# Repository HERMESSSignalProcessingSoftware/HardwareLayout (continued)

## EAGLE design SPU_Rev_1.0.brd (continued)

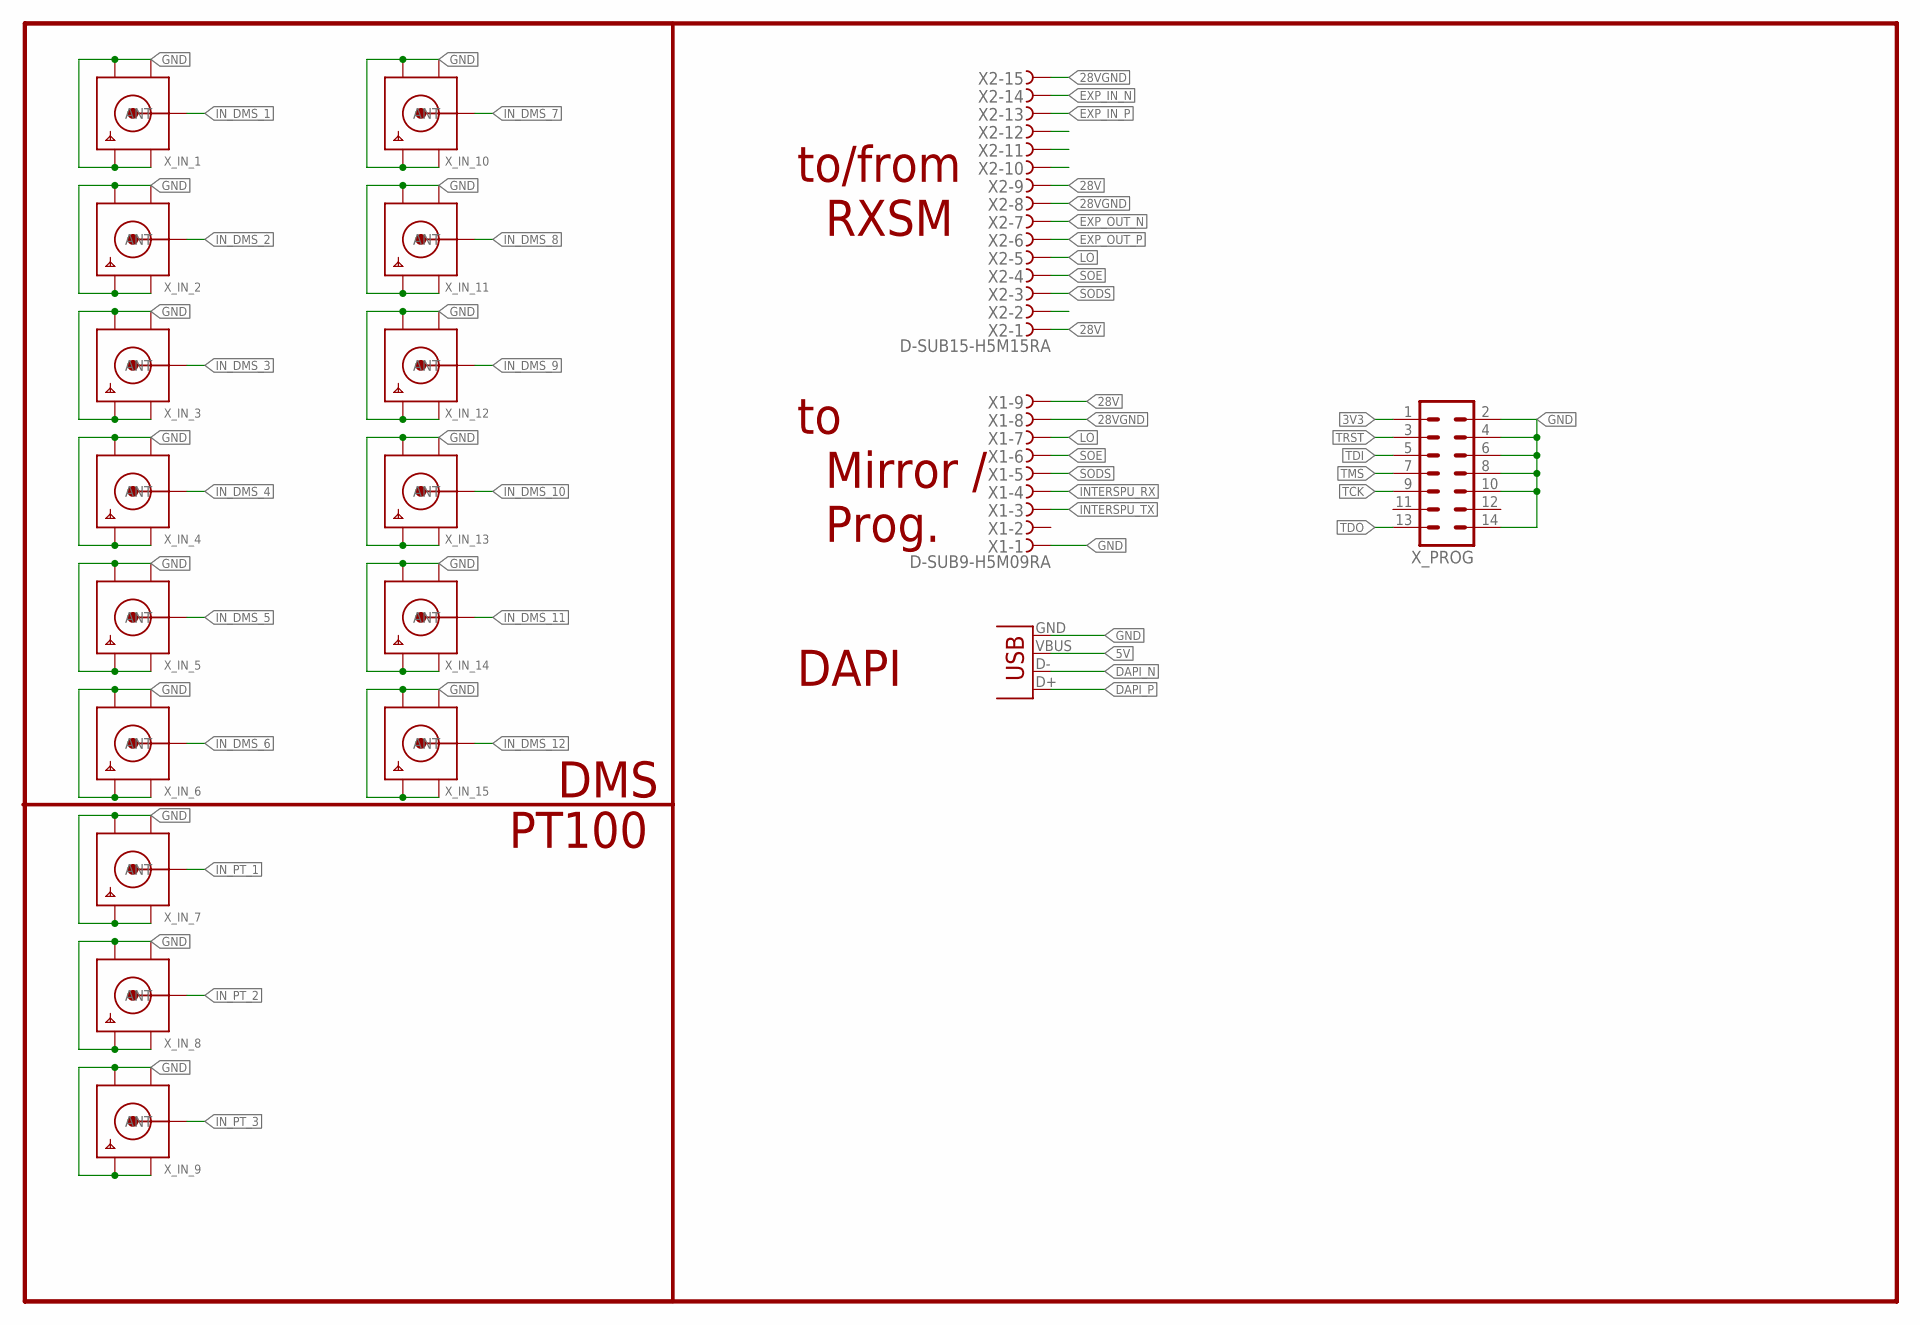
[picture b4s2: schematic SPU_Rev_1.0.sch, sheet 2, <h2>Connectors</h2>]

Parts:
X1: D-SUB9-H5M09RA; H5M09RA
X2: D-SUB15-H5M15RA; H5M15RA
X3: USBPTH; USB-B-PTH
X_IN_1, X_IN_2, X_IN_3, X_IN_4, X_IN_5, X_IN_6, X_IN_7, X_IN_8, X_IN_9, X_IN_10, X_IN_11, X_IN_12, X_IN_13, X_IN_14, X_IN_15: SMACONNECTOR_EDGE; SMA_EDGELAUNCH
X_PROG: MA07-2

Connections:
3V3: X_PROG.1; also elsewhere on the board
5V: X3.VBUS; also elsewhere on the board
28V: X1.9, X2.1, X2.9; also elsewhere on the board
28VGND: X1.8, X2.8, X2.15; also elsewhere on the board
DAPI_N: X3.D-; also elsewhere on the board
DAPI_P: X3.D+; also elsewhere on the board
EXP_IN_N: X2.14; also elsewhere on the board
EXP_IN_P: X2.13; also elsewhere on the board
EXP_OUT_N: X2.7; also elsewhere on the board
EXP_OUT_P: X2.6; also elsewhere on the board
GND: X1.1, X3.GND, X_IN_1.GND@1 (GND4), X_IN_1.GND@2 (GND3), X_IN_1.GND@3 (GND2), X_IN_1.GND@4 (GND1), X_IN_2.GND@1 (GND4), X_IN_2.GND@2 (GND3), X_IN_2.GND@3 (GND2), X_IN_2.GND@4 (GND1), X_IN_3.GND@1 (GND4), X_IN_3.GND@2 (GND3), X_IN_3.GND@3 (GND2), X_IN_3.GND@4 (GND1), X_IN_4.GND@1 (GND4), X_IN_4.GND@2 (GND3), X_IN_4.GND@3 (GND2), X_IN_4.GND@4 (GND1), X_IN_5.GND@1 (GND4), X_IN_5.GND@2 (GND3), X_IN_5.GND@3 (GND2), X_IN_5.GND@4 (GND1), X_IN_6.GND@1 (GND4), X_IN_6.GND@2 (GND3), X_IN_6.GND@3 (GND2), X_IN_6.GND@4 (GND1), X_IN_7.GND@1 (GND4), X_IN_7.GND@2 (GND3), X_IN_7.GND@3 (GND2), X_IN_7.GND@4 (GND1), X_IN_8.GND@1 (GND4), X_IN_8.GND@2 (GND3), X_IN_8.GND@3 (GND2), X_IN_8.GND@4 (GND1), X_IN_9.GND@1 (GND4), X_IN_9.GND@2 (GND3), X_IN_9.GND@3 (GND2), X_IN_9.GND@4 (GND1), X_IN_10.GND@1 (GND4), X_IN_10.GND@2 (GND3), X_IN_10.GND@3 (GND2), X_IN_10.GND@4 (GND1), X_IN_11.GND@1 (GND4), X_IN_11.GND@2 (GND3), X_IN_11.GND@3 (GND2), X_IN_11.GND@4 (GND1), X_IN_12.GND@1 (GND4), X_IN_12.GND@2 (GND3), X_IN_12.GND@3 (GND2), X_IN_12.GND@4 (GND1), X_IN_13.GND@1 (GND4), X_IN_13.GND@2 (GND3), X_IN_13.GND@3 (GND2), X_IN_13.GND@4 (GND1), X_IN_14.GND@1 (GND4), X_IN_14.GND@2 (GND3), X_IN_14.GND@3 (GND2), X_IN_14.GND@4 (GND1), X_IN_15.GND@1 (GND4), X_IN_15.GND@2 (GND3), X_IN_15.GND@3 (GND2), X_IN_15.GND@4 (GND1), X_PROG.2, X_PROG.4, X_PROG.6, X_PROG.8, X_PROG.10, X_PROG.14; also elsewhere on the board
INTERSPU_RX: X1.4; also elsewhere on the board
INTERSPU_TX: X1.3; also elsewhere on the board
IN_DMS_1: X_IN_1.P (ANT); also elsewhere on the board
IN_DMS_2: X_IN_2.P (ANT); also elsewhere on the board
IN_DMS_3: X_IN_3.P (ANT); also elsewhere on the board
IN_DMS_4: X_IN_4.P (ANT); also elsewhere on the board
IN_DMS_5: X_IN_5.P (ANT); also elsewhere on the board
IN_DMS_6: X_IN_6.P (ANT); also elsewhere on the board
IN_DMS_7: X_IN_10.P (ANT); also elsewhere on the board
IN_DMS_8: X_IN_11.P (ANT); also elsewhere on the board
IN_DMS_9: X_IN_12.P (ANT); also elsewhere on the board
IN_DMS_10: X_IN_13.P (ANT); also elsewhere on the board
IN_DMS_11: X_IN_14.P (ANT); also elsewhere on the board
IN_DMS_12: X_IN_15.P (ANT); also elsewhere on the board
IN_PT_1: X_IN_7.P (ANT); also elsewhere on the board
IN_PT_2: X_IN_8.P (ANT); also elsewhere on the board
IN_PT_3: X_IN_9.P (ANT); also elsewhere on the board
LO: X1.7, X2.5; also elsewhere on the board
SODS: X1.5, X2.3; also elsewhere on the board
SOE: X1.6, X2.4; also elsewhere on the board
TCK: X_PROG.9; also elsewhere on the board
TDI: X_PROG.5; also elsewhere on the board
TDO: X_PROG.13; also elsewhere on the board
TMS: X_PROG.7; also elsewhere on the board
TRST: X_PROG.3; also elsewhere on the board

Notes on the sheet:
DMS
PT100
DAPI
to/from RXSM
to Mirror / Prog.

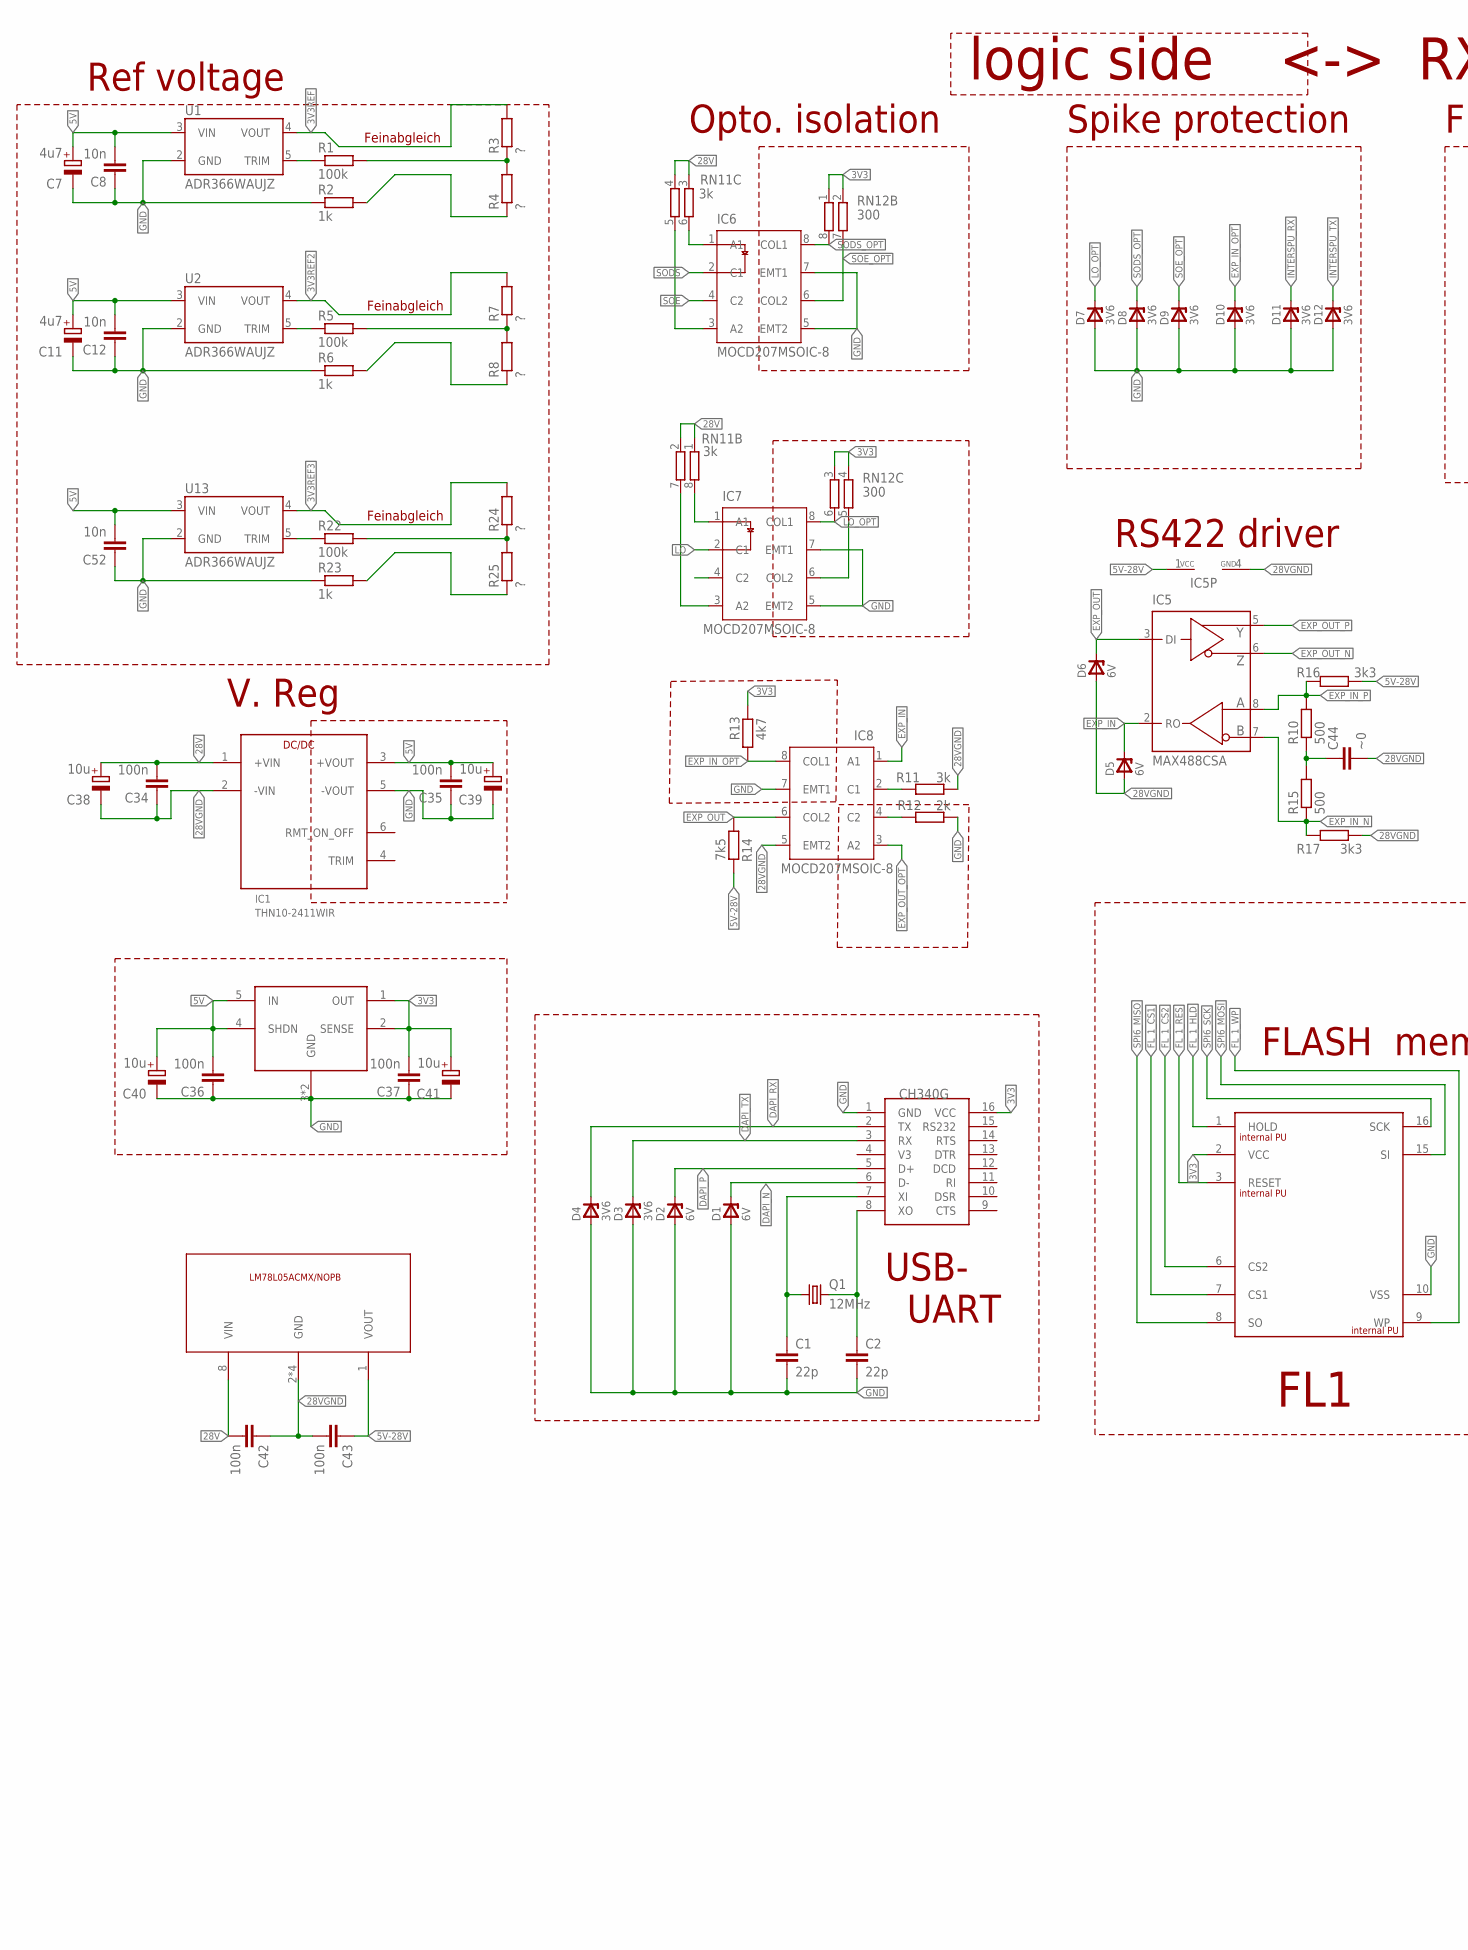
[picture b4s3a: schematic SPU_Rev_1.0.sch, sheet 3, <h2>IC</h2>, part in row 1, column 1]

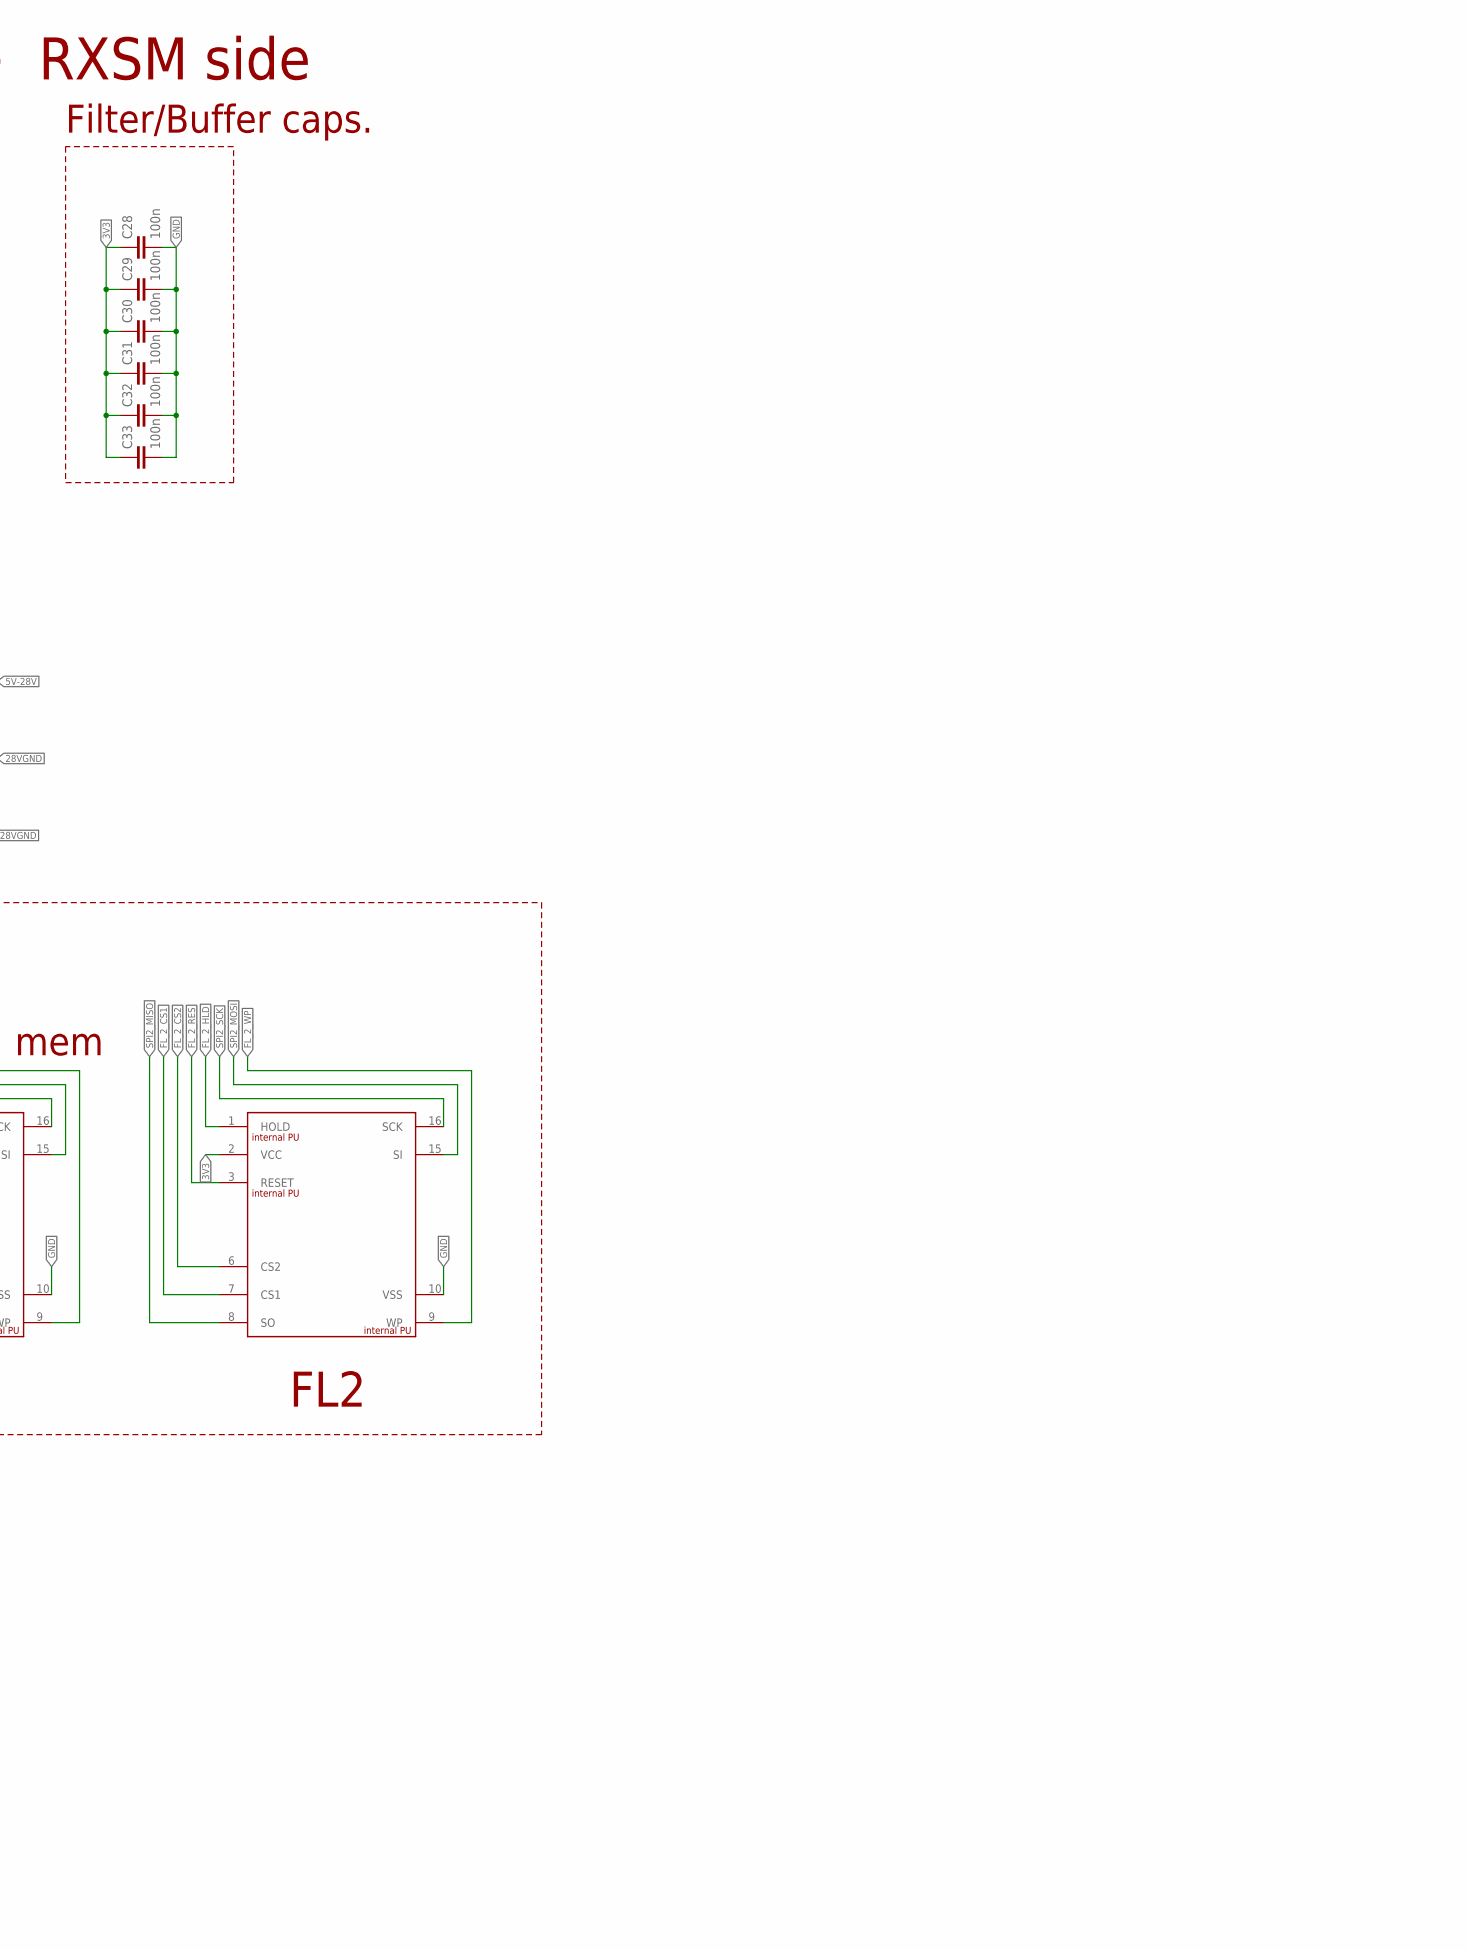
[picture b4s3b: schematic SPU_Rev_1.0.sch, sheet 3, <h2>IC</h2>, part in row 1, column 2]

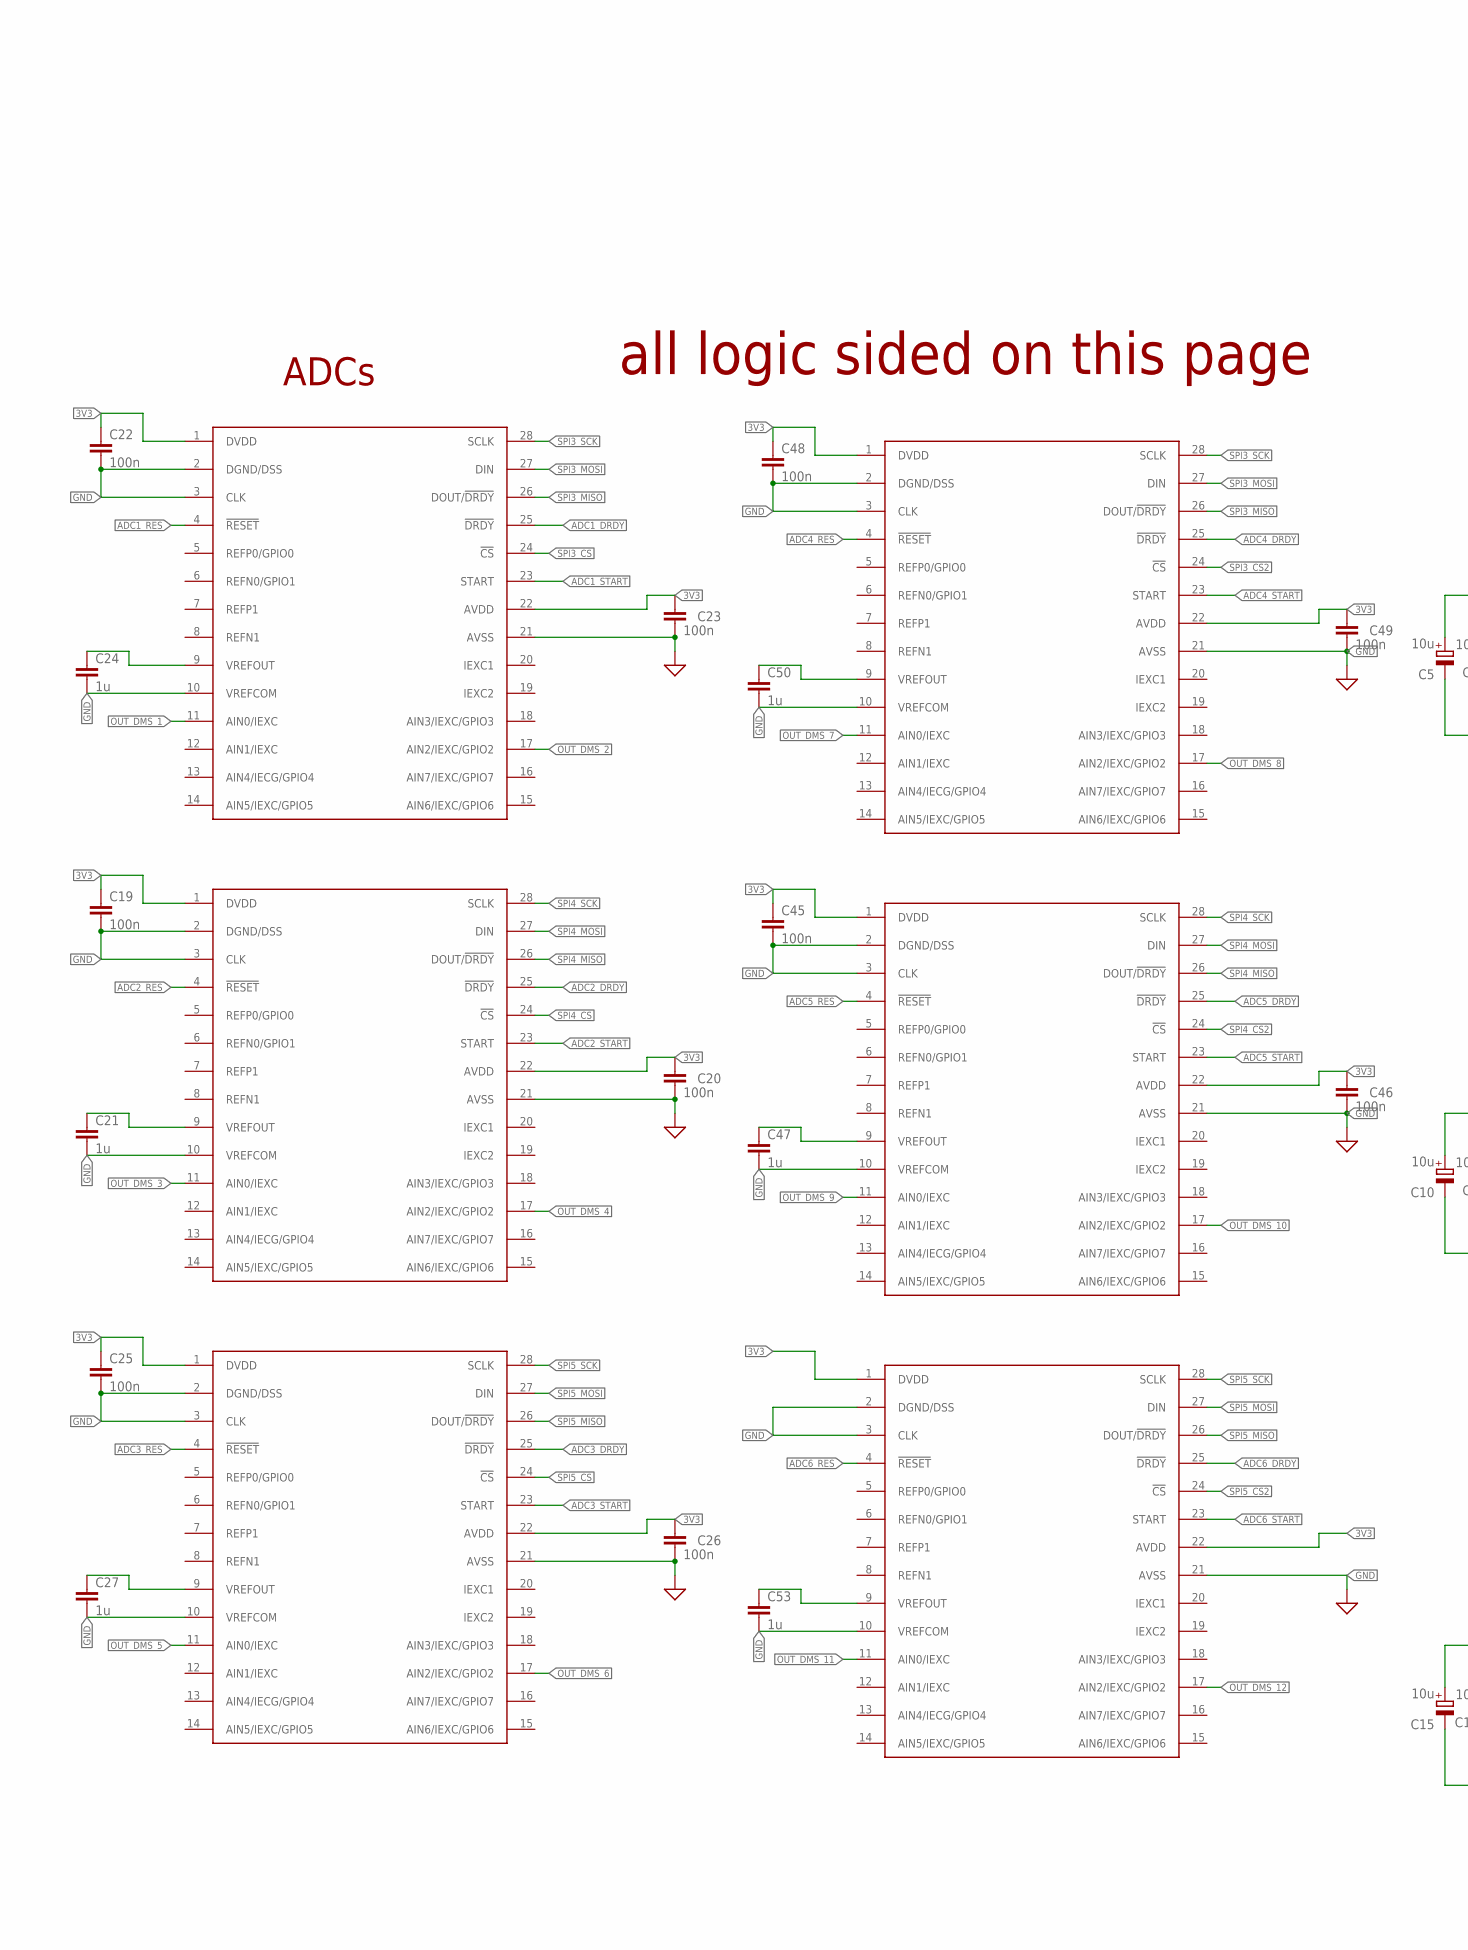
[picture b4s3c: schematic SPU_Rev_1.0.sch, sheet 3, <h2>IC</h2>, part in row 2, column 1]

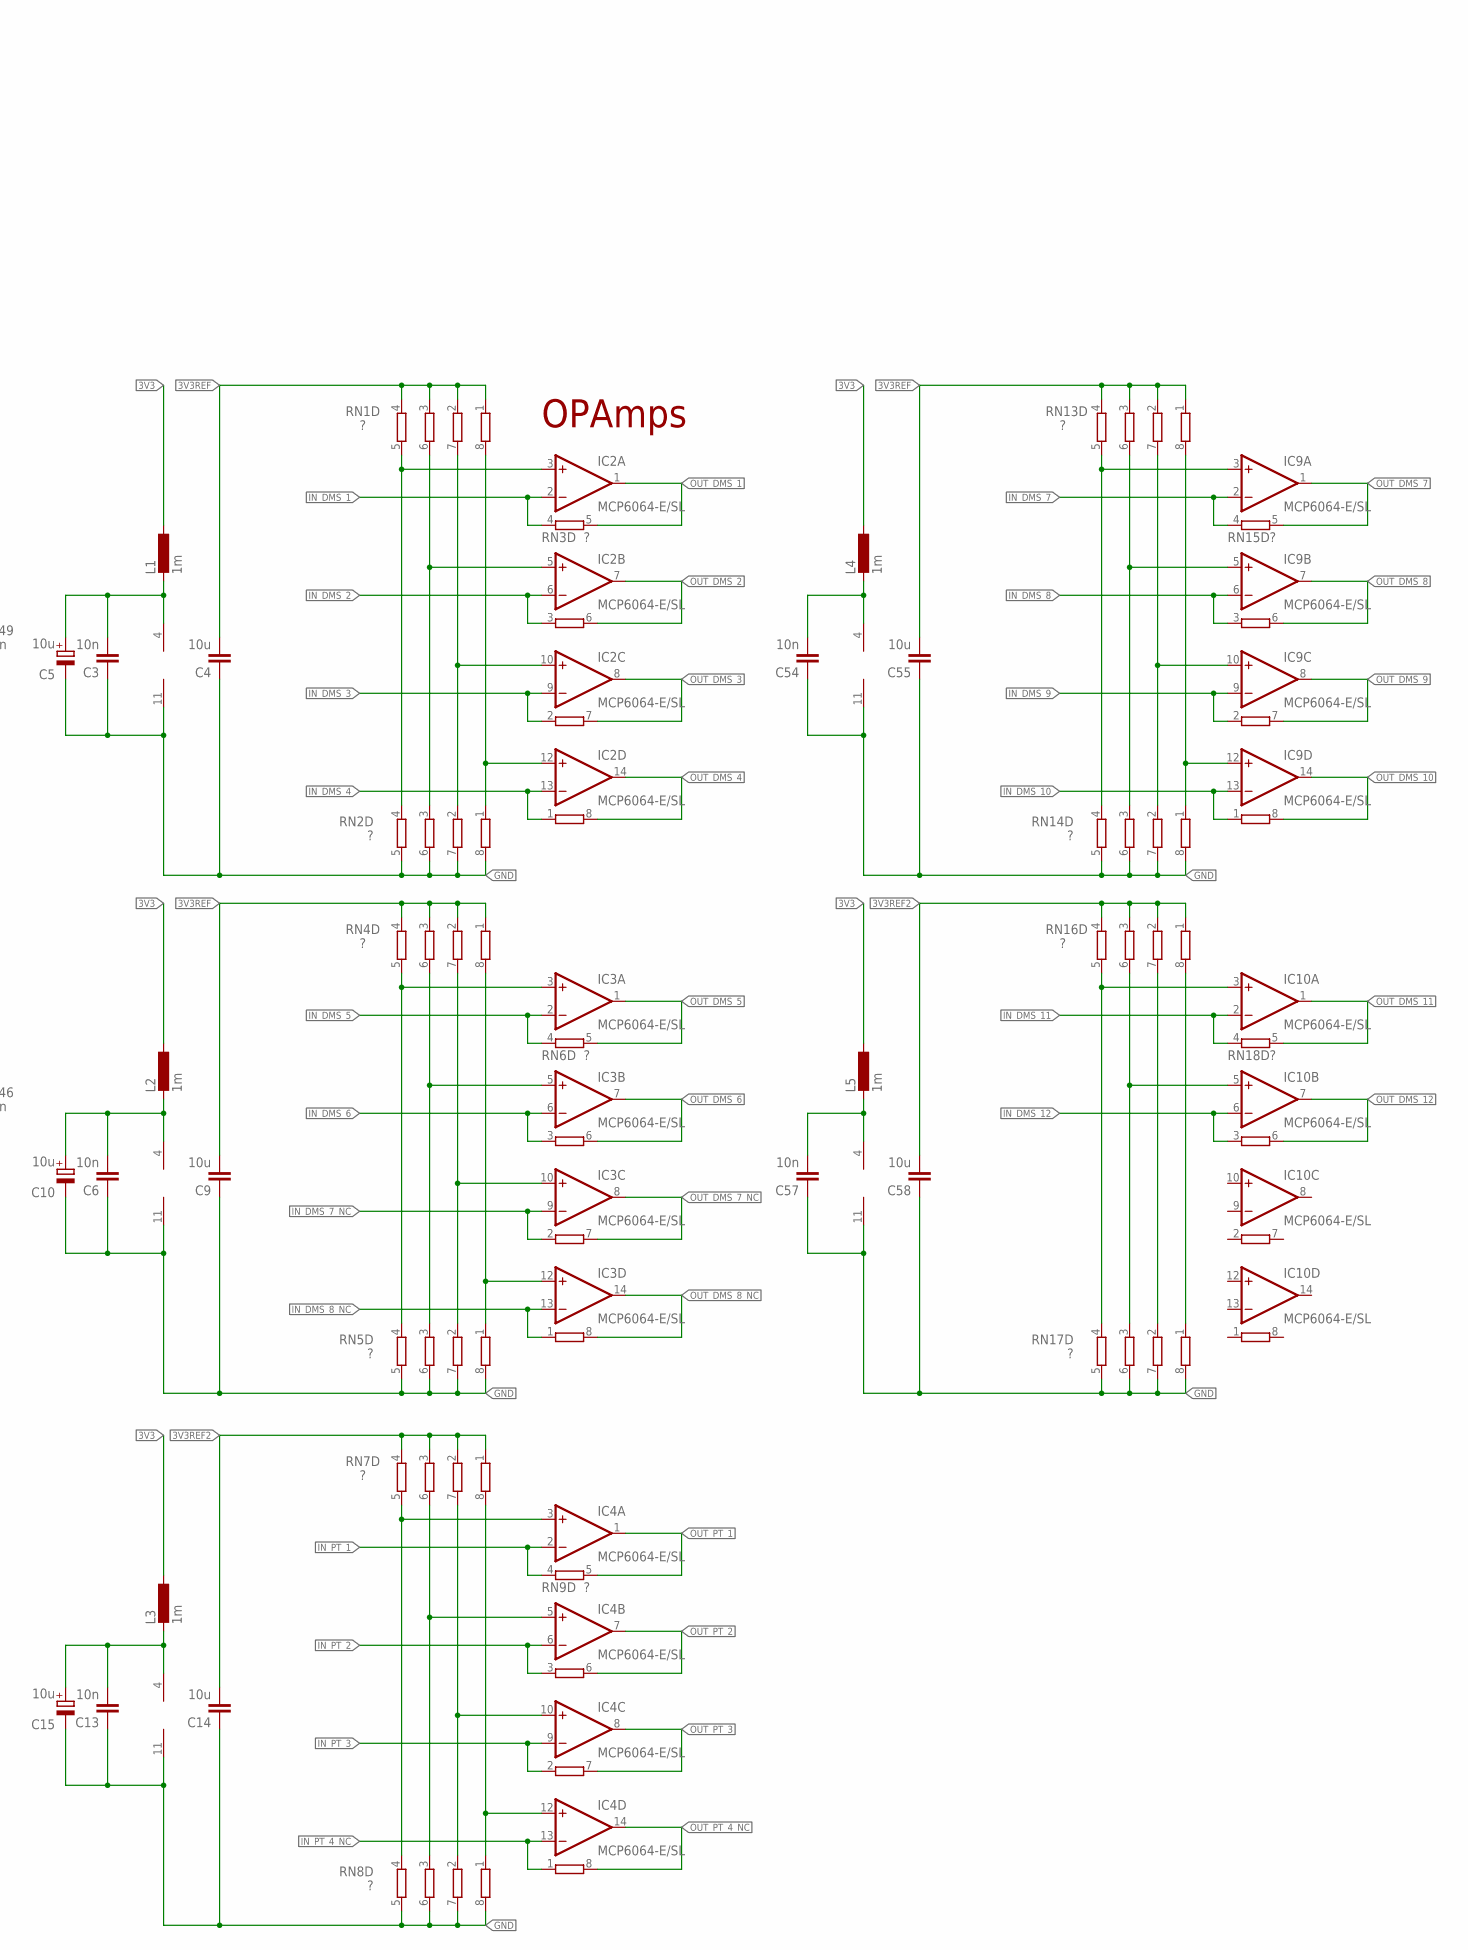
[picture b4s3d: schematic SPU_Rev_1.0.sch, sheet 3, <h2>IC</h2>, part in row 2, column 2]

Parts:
C1, C2: 22p; C0603
C3, C6, C8, C12, C13, C52, C54, C57: 10n; C0805
C4, C9, C14, C55, C58: 10u; C0805
C5, C10, C15, C38, C39, C40, C41: 10u; 153CLV-0810
C7, C11: 4u7; 153CLV-0810
C19, C20, C22, C23, C25, C26, C28, C29, C30, C31, C32, C33, C34, C35, C36, C37, C42, C43, C45, C46, C48, C49: 100n; C0805
C21, C24, C27, C47, C50, C53: 1u; C0805
C44: ~0; C0805
D1, D2, D5, D6: 6V; DMELF
D3, D4, D7, D8, D9, D10, D11, D12: 3V6; DMELF
IC1: THN10-2411WIR; THL_20WI_SERIES
IC2, IC3, IC4, IC9, IC10: MCP6064-E/SL; SO14
IC5: MAX488CSA; SO08
IC6, IC7, IC8: MOCD207MSOIC-8; SOIC127P594X363-8N
IC12: LM78L05ACMX/NOPB; SOIC8
IC13: CH340G; SOIC16
L1, L2, L3, L4, L5: 1m; L5650M
Q1: 12MHz; SM49
R1, R5, R22: 100k; R0805
R2, R6, R23: 1k; R0805
R3, R4, R7, R8, R24, R25: ?; R0805
R10, R15: 500; R0805
R11: 3k; R0805
R12: 2k; R0805
R13: 4k7; R0805
R14: 7k5; R0805
R16, R17: 3k3; R0805
RN1, RN2, RN3, RN4, RN5, RN6, RN7, RN8, RN9, RN13, RN14, RN15, RN16, RN17, RN18: ?; EXBS8V
RN11: 3k; EXBS8V
RN12: 300; EXBS8V
U1, U2, U13: ADR366WAUJZ; SOT23-5
U3, U4, U5, U10, U11, U12: ADS1148QPWRQ1; TSSOP28
U6: LT1528; Q5-DD
U7, U8: S70FL01GS; SO16

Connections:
3V3: C19.1, C20.1, C22.1, C23.1, C25.1, C26.1, C28.1, C29.1, C30.1, C31.1, C32.1, C33.1, C37.2, C41.+, C45.1, C46.1, C48.1, C49.1, IC13.16 (VCC), L1.1, L2.1, L3.1, L4.1, L5.1, R13.2, RN12.1, RN12.2 (1), RN12.3 (1), RN12.4 (1), U3.1 (DVDD), U3.22 (AVDD), U4.1 (DVDD), U4.22 (AVDD), U5.1 (DVDD), U5.22 (AVDD), U6.1 (OUT), U6.2 (SENSE), U7.2 (VCC), U8.2 (VCC), U10.1 (DVDD), U10.22 (AVDD), U11.1 (DVDD), U11.22 (AVDD), U12.1 (DVDD), U12.22 (AVDD); also elsewhere on the board
3V3REF: C4.2, C9.2, C55.2, R3.2, RN1.1, RN1.2 (1), RN1.3 (1), RN1.4 (1), RN4.1, RN4.2 (1), RN4.3 (1), RN4.4 (1), RN13.1, RN13.2 (1), RN13.3 (1), RN13.4 (1), U1.4 (VOUT)
3V3REF2: C14.2, C58.2, R7.2, RN7.1, RN7.2 (1), RN7.3 (1), RN7.4 (1), RN16.1, RN16.2 (1), RN16.3 (1), RN16.4 (1), U2.4 (VOUT)
3V3REF3: R24.2, U13.4 (VOUT); also elsewhere on the board
5V: C7.+, C8.2, C11.+, C12.2, C35.2, C36.2, C39.+, C40.+, C52.2, IC1.3 (+VOUT), U1.3 (VIN), U2.3 (VIN), U6.4 (SHDN), U6.5 (IN), U13.3 (VIN); also elsewhere on the board
5V-28V: C43.1, IC5.1 (VCC), IC12.1 (VOUT), R14.2, R16.1; also elsewhere on the board
28V: C34.2, C38.+, C42.2, IC1.1 (+VIN), IC12.8 (VIN), RN11.1, RN11.2 (1), RN11.3 (1), RN11.4 (1); also elsewhere on the board
28VGND: C34.1, C38.-, C42.1, C43.2, C44.2, D5.A, D6.A, IC1.2 (-VIN), IC5.4 (GND), IC8.5 (EMT2), IC12.2 (GND), IC12.3 (GND), IC12.6 (GND), IC12.7 (GND), R11.1, R17.1; also elsewhere on the board
ADC1_DRDY: U4.25 (!DRDY); also elsewhere on the board
ADC1_RES: U4.4 (!RESET); also elsewhere on the board
ADC1_START: U4.23 (START); also elsewhere on the board
ADC2_DRDY: U3.25 (!DRDY); also elsewhere on the board
ADC2_RES: U3.4 (!RESET); also elsewhere on the board
ADC2_START: U3.23 (START); also elsewhere on the board
ADC3_DRDY: U5.25 (!DRDY); also elsewhere on the board
ADC3_RES: U5.4 (!RESET); also elsewhere on the board
ADC3_START: U5.23 (START); also elsewhere on the board
ADC4_DRDY: U11.25 (!DRDY); also elsewhere on the board
ADC4_RES: U11.4 (!RESET); also elsewhere on the board
ADC4_START: U11.23 (START); also elsewhere on the board
ADC5_DRDY: U10.25 (!DRDY); also elsewhere on the board
ADC5_RES: U10.4 (!RESET); also elsewhere on the board
ADC5_START: U10.23 (START); also elsewhere on the board
ADC6_DRDY: U12.25 (!DRDY); also elsewhere on the board
ADC6_RES: U12.4 (!RESET); also elsewhere on the board
ADC6_START: U12.23 (START); also elsewhere on the board
DAPI_N: D1.C, IC13.6 (D-); also elsewhere on the board
DAPI_P: D2.C, IC13.5 (D+); also elsewhere on the board
DAPI_RX: D4.C, IC13.2 (TX); also elsewhere on the board
DAPI_TX: D3.C, IC13.3 (RX); also elsewhere on the board
EXP_IN: D5.C, IC5.2 (RO), IC8.1 (A1)
EXP_IN_N: IC5.7 (B), R15.1, R17.2; also elsewhere on the board
EXP_IN_OPT: D10.C, IC8.8 (COL1), R13.1; also elsewhere on the board
EXP_IN_P: IC5.8 (A), R10.2, R16.2; also elsewhere on the board
EXP_OUT: D6.C, IC5.3 (DI), IC8.6 (COL2), R14.1
EXP_OUT_N: IC5.6 (Z); also elsewhere on the board
EXP_OUT_OPT: IC8.3 (A2); also elsewhere on the board
EXP_OUT_P: IC5.5 (Y); also elsewhere on the board
FL_1_CS1: U7.7 (CS1); also elsewhere on the board
FL_1_CS2: U7.6 (CS2); also elsewhere on the board
FL_1_HLD: U7.1 (HOLD); also elsewhere on the board
FL_1_RES: U7.3 (RESET); also elsewhere on the board
FL_1_WP: U7.9 (WP); also elsewhere on the board
FL_2_CS1: U8.7 (CS1); also elsewhere on the board
FL_2_CS2: U8.6 (CS2); also elsewhere on the board
FL_2_HLD: U8.1 (HOLD); also elsewhere on the board
FL_2_RES: U8.3 (RESET); also elsewhere on the board
FL_2_WP: U8.9 (WP); also elsewhere on the board
GND: C1.2, C2.2, C3.1, C4.1, C5.-, C6.1, C7.-, C8.1, C9.1, C10.-, C11.-, C12.1, C13.1, C14.1, C15.-, C19.2, C20.2, C21.2, C22.2, C23.2, C24.2, C25.2, C26.2, C27.2, C28.2, C29.2, C30.2, C31.2, C32.2, C33.2, C35.1, C36.1, C37.1, C39.-, C40.-, C41.-, C45.2, C46.2, C47.2, C48.2, C49.2, C50.2, C52.1, C53.2, C54.1, C55.1, C57.1, C58.1, D1.A, D2.A, D3.A, D4.A, D7.A, D8.A, D9.A, D10.A, D11.A, D12.A, IC1.5 (-VOUT), IC2.11 (V-), IC3.11 (V-), IC4.11 (V-), IC6.5 (EMT2), IC6.7 (EMT1), IC7.5 (EMT2), IC7.7 (EMT1), IC8.7 (EMT1), IC9.11 (V-), IC10.11 (V-), IC13.1 (GND), R2.1, R6.1, R12.1, R23.1, RN2.5 (2), RN2.6 (2), RN2.7 (2), RN2.8 (2), RN5.5 (2), RN5.6 (2), RN5.7 (2), RN5.8 (2), RN8.5 (2), RN8.6 (2), RN8.7 (2), RN8.8 (2), RN14.5 (2), RN14.6 (2), RN14.7 (2), RN14.8 (2), RN17.5 (2), RN17.6 (2), RN17.7 (2), RN17.8 (2), U1.2 (GND), U2.2 (GND), U3.2 (DGND/DSS), U3.3 (CLK), U3.10 (VREFCOM), U3.21 (AVSS), U4.2 (DGND/DSS), U4.3 (CLK), U4.10 (VREFCOM), U4.21 (AVSS), U5.2 (DGND/DSS), U5.3 (CLK), U5.10 (VREFCOM), U5.21 (AVSS), U6.3 (GND), U6.6 (GND), U7.10 (VSS), U8.10 (VSS), U10.2 (DGND/DSS), U10.3 (CLK), U10.10 (VREFCOM), U10.21 (AVSS), U11.2 (DGND/DSS), U11.3 (CLK), U11.10 (VREFCOM), U11.21 (AVSS), U12.2 (DGND/DSS), U12.3 (CLK), U12.10 (VREFCOM), U12.21 (AVSS), U13.2 (GND); also elsewhere on the board
INTERSPU_RX: D11.C; also elsewhere on the board
INTERSPU_TX: D12.C; also elsewhere on the board
IN_DMS_1: IC2.2 (-IN), RN3.4 (1); also elsewhere on the board
IN_DMS_2: IC2.6 (-IN), RN3.3 (1); also elsewhere on the board
IN_DMS_3: IC2.9 (-IN), RN3.2 (1); also elsewhere on the board
IN_DMS_4: IC2.13 (-IN), RN3.1; also elsewhere on the board
IN_DMS_5: IC3.2 (-IN), RN6.4 (1); also elsewhere on the board
IN_DMS_6: IC3.6 (-IN), RN6.3 (1); also elsewhere on the board
IN_DMS_7: IC9.2 (-IN), RN15.4 (1); also elsewhere on the board
IN_DMS_7_NC: IC3.9 (-IN), RN6.2 (1)
IN_DMS_8: IC9.6 (-IN), RN15.3 (1); also elsewhere on the board
IN_DMS_8_NC: IC3.13 (-IN), RN6.1
IN_DMS_9: IC9.9 (-IN), RN15.2 (1); also elsewhere on the board
IN_DMS_10: IC9.13 (-IN), RN15.1; also elsewhere on the board
IN_DMS_11: IC10.2 (-IN), RN18.4 (1); also elsewhere on the board
IN_DMS_12: IC10.6 (-IN), RN18.3 (1); also elsewhere on the board
IN_PT_1: IC4.2 (-IN), RN9.4 (1); also elsewhere on the board
IN_PT_2: IC4.6 (-IN), RN9.3 (1); also elsewhere on the board
IN_PT_3: IC4.9 (-IN), RN9.2 (1); also elsewhere on the board
IN_PT_4_NC: IC4.13 (-IN), RN9.1
LO: IC7.2 (C1); also elsewhere on the board
LO_OPT: D7.C, IC7.8 (COL1), RN12.6 (2); also elsewhere on the board
unnamed: C2.1, IC13.8 (XO), Q1.2
unnamed: C1.1, IC13.7 (XI), Q1.1
unnamed: R1.2, R3.1, R4.2
unnamed: R1.1, U1.5 (TRIM)
unnamed: R2.2, R4.1
unnamed: IC2.3 (+IN), RN1.5 (2), RN2.4 (1)
unnamed: IC2.5 (+IN), RN1.6 (2), RN2.3 (1)
unnamed: IC2.10 (+IN), RN1.7 (2), RN2.2 (1)
unnamed: IC2.12 (+IN), RN1.8 (2), RN2.1
unnamed: C3.2, C5.+, IC2.4 (V+), L1.2
unnamed: IC3.3 (+IN), RN4.5 (2), RN5.4 (1)
unnamed: IC3.5 (+IN), RN4.6 (2), RN5.3 (1)
unnamed: IC3.10 (+IN), RN4.7 (2), RN5.2 (1)
unnamed: IC3.12 (+IN), RN4.8 (2), RN5.1
unnamed: C6.2, C10.+, IC3.4 (V+), L2.2
unnamed: R5.1, U2.5 (TRIM)
unnamed: R5.2, R7.1, R8.2
unnamed: R6.2, R8.1
unnamed: IC4.3 (+IN), RN7.5 (2), RN8.4 (1)
unnamed: IC4.5 (+IN), RN7.6 (2), RN8.3 (1)
unnamed: IC4.10 (+IN), RN7.7 (2), RN8.2 (1)
unnamed: IC4.12 (+IN), RN7.8 (2), RN8.1
unnamed: C13.2, C15.+, IC4.4 (V+), L3.2
unnamed: C21.1, U3.9 (VREFOUT)
unnamed: C24.1, U4.9 (VREFOUT)
unnamed: C27.1, U5.9 (VREFOUT)
unnamed: IC6.1 (A1), RN11.6 (2)
unnamed: IC6.3 (A2), RN11.5 (2)
unnamed: IC8.4 (C2), R12.2
unnamed: IC7.6 (COL2), RN12.5 (2)
unnamed: IC7.1 (A1), RN11.8 (2)
unnamed: IC7.3 (A2), RN11.7 (2)
unnamed: IC8.2 (C1), R11.2
unnamed: C44.1, R10.1, R15.2
unnamed: C47.1, U10.9 (VREFOUT)
unnamed: C50.1, U11.9 (VREFOUT)
unnamed: C53.1, U12.9 (VREFOUT)
unnamed: IC9.3 (+IN), RN13.5 (2), RN14.4 (1)
unnamed: IC9.5 (+IN), RN13.6 (2), RN14.3 (1)
unnamed: IC9.10 (+IN), RN13.7 (2), RN14.2 (1)
unnamed: IC9.12 (+IN), RN13.8 (2), RN14.1
unnamed: C54.2, IC9.4 (V+), L4.2
unnamed: IC10.3 (+IN), RN16.5 (2), RN17.4 (1)
unnamed: IC10.5 (+IN), RN16.6 (2), RN17.3 (1)
unnamed: RN16.7 (2), RN17.2 (1)
unnamed: RN16.8 (2), RN17.1
unnamed: C57.2, IC10.4 (V+), L5.2
unnamed: R22.1, U13.5 (TRIM)
unnamed: R22.2, R24.1, R25.2
unnamed: R23.2, R25.1
OUT_DMS_1: IC2.1 (OUT), RN3.5 (2), U4.11 (AIN0/IEXC)
OUT_DMS_2: IC2.7 (OUT), RN3.6 (2), U4.17 (AIN2/IEXC/GPIO2)
OUT_DMS_3: IC2.8 (OUT), RN3.7 (2), U3.11 (AIN0/IEXC)
OUT_DMS_4: IC2.14 (OUT), RN3.8 (2), U3.17 (AIN2/IEXC/GPIO2)
OUT_DMS_5: IC3.1 (OUT), RN6.5 (2), U5.11 (AIN0/IEXC)
OUT_DMS_6: IC3.7 (OUT), RN6.6 (2), U5.17 (AIN2/IEXC/GPIO2)
OUT_DMS_7: IC9.1 (OUT), RN15.5 (2), U11.11 (AIN0/IEXC)
OUT_DMS_7_NC: IC3.8 (OUT), RN6.7 (2)
OUT_DMS_8: IC9.7 (OUT), RN15.6 (2), U11.17 (AIN2/IEXC/GPIO2)
OUT_DMS_8_NC: IC3.14 (OUT), RN6.8 (2)
OUT_DMS_9: IC9.8 (OUT), RN15.7 (2), U10.11 (AIN0/IEXC)
OUT_DMS_10: IC9.14 (OUT), RN15.8 (2), U10.17 (AIN2/IEXC/GPIO2)
OUT_DMS_11: IC10.1 (OUT), RN18.5 (2), U12.11 (AIN0/IEXC)
OUT_DMS_12: IC10.7 (OUT), RN18.6 (2), U12.17 (AIN2/IEXC/GPIO2)
OUT_PT_1: IC4.1 (OUT), RN9.5 (2); also elsewhere on the board
OUT_PT_2: IC4.7 (OUT), RN9.6 (2); also elsewhere on the board
OUT_PT_3: IC4.8 (OUT), RN9.7 (2); also elsewhere on the board
OUT_PT_4_NC: IC4.14 (OUT), RN9.8 (2)
SODS: IC6.2 (C1); also elsewhere on the board
SODS_OPT: D8.C, IC6.8 (COL1), RN12.8 (2); also elsewhere on the board
SOE: IC6.4 (C2); also elsewhere on the board
SOE_OPT: D9.C, IC6.6 (COL2), RN12.7 (2); also elsewhere on the board
SPI2_MISO: U8.8 (SO); also elsewhere on the board
SPI2_MOSI: U8.15 (SI); also elsewhere on the board
SPI2_SCK: U8.16 (SCK); also elsewhere on the board
SPI3_CS: U4.24 (!CS); also elsewhere on the board
SPI3_CS2: U11.24 (!CS); also elsewhere on the board
SPI3_MISO: U4.26 (DOUT/!DRDY), U11.26 (DOUT/!DRDY); also elsewhere on the board
SPI3_MOSI: U4.27 (DIN), U11.27 (DIN); also elsewhere on the board
SPI3_SCK: U4.28 (SCLK), U11.28 (SCLK); also elsewhere on the board
SPI4_CS: U3.24 (!CS); also elsewhere on the board
SPI4_CS2: U10.24 (!CS); also elsewhere on the board
SPI4_MISO: U3.26 (DOUT/!DRDY), U10.26 (DOUT/!DRDY); also elsewhere on the board
SPI4_MOSI: U3.27 (DIN), U10.27 (DIN); also elsewhere on the board
SPI4_SCK: U3.28 (SCLK), U10.28 (SCLK); also elsewhere on the board
SPI5_CS: U5.24 (!CS); also elsewhere on the board
SPI5_CS2: U12.24 (!CS); also elsewhere on the board
SPI5_MISO: U5.26 (DOUT/!DRDY), U12.26 (DOUT/!DRDY); also elsewhere on the board
SPI5_MOSI: U5.27 (DIN), U12.27 (DIN); also elsewhere on the board
SPI5_SCK: U5.28 (SCLK), U12.28 (SCLK); also elsewhere on the board
SPI6_MISO: U7.8 (SO); also elsewhere on the board
SPI6_MOSI: U7.15 (SI); also elsewhere on the board
SPI6_SCK: U7.16 (SCK); also elsewhere on the board

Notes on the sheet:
Ref voltage
Feinabgleich
OPAmps
FL1
FL2
ADCs
USB- UART
FLASH mem
V. Reg
LM78L05ACMX/NOPB
RS422 driver
logic side <-> RXSM side
Opto. isolation
Spike protection
Filter/Buffer caps.
all logic sided on this page
